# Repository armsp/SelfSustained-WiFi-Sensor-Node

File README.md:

# Self Sustained WiFi Sensor Node using CC3200 SoC and Energy Harvesting with BQ25505/BQ25570
Complete Details regarding the project can be found at my Blog https://shantamraj.wordpress.com
You can also visit my Hackster.io profile for the same at https://www.hackster.io/shantam

I am working on taking this project and the overall idea behind it to next level. The updates regarding that will be posted soon.

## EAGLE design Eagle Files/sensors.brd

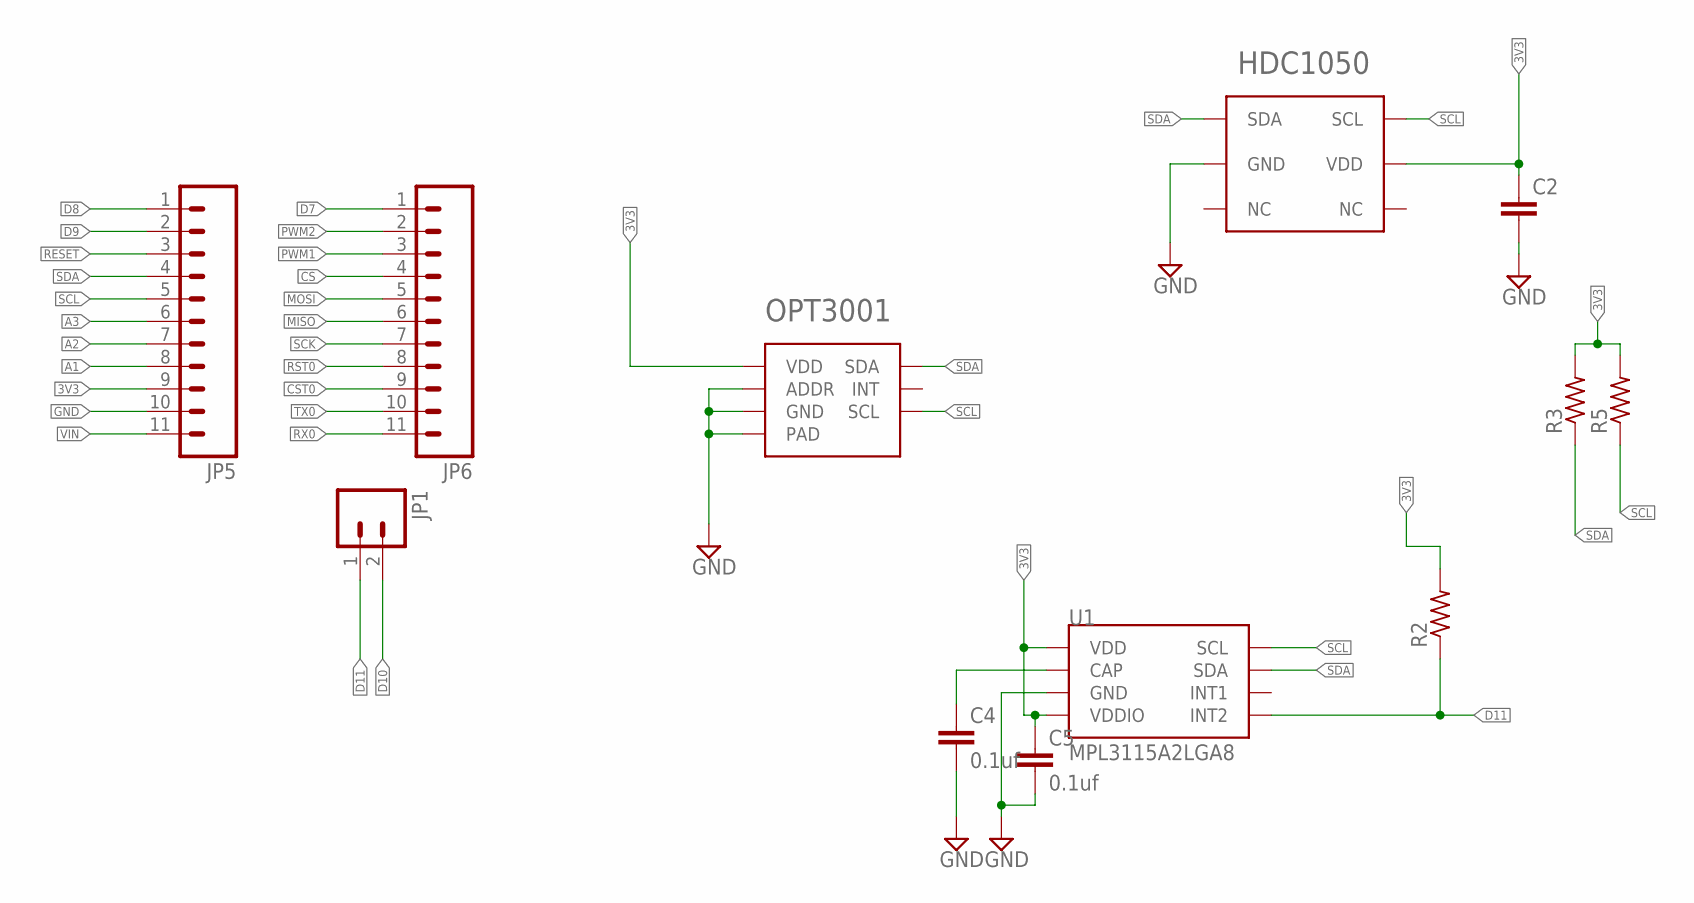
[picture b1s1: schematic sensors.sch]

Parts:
C2: C-EUC0805; C0805
C4, C5: 0.1uf; C0805
HDC1050: HDC1050; PWSON-6
JP1: M02PTH; 1X02
JP5, JP6: M11PTH; 1X11
OPT3001: OPT3001
R2, R3, R5: R-US_0204/5; 0204/5
U1: MPL3115A2LGA8; LGA8

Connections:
3V3: C2.1, C5.1, HDC1050.P$5 (VDD), JP5.9, OPT3001.P$1 (VDD), R2.2, R3.2, R5.2, U1.1 (VDD), U1.4 (VDDIO)
A1: JP5.8
A2: JP5.7
A3: JP5.6
CS: JP6.4
CST0: JP6.9
D7: JP6.1
D8: JP5.1
D9: JP5.2
D10: JP1.2
D11: JP1.1, R2.1, U1.5 (INT2)
GND: C2.2, C4.2, C5.2, HDC1050.P$2 (GND), JP5.10, OPT3001.P$2 (ADDR), OPT3001.P$3 (GND), OPT3001.P$7 (PAD), U1.3 (GND)
MISO: JP6.6
MOSI: JP6.5
unnamed: C4.1, U1.2 (CAP)
PWM1: JP6.3
PWM2: JP6.2
RESET: JP5.3
RST0: JP6.8
RX0: JP6.11
SCK: JP6.7
SCL: HDC1050.P$6 (SCL), JP5.5, OPT3001.P$4 (SCL), R5.1, U1.8 (SCL)
SDA: HDC1050.P$1 (SDA), JP5.4, OPT3001.P$6 (SDA), R3.1, U1.7 (SDA)
TX0: JP6.10
VIN: JP5.11

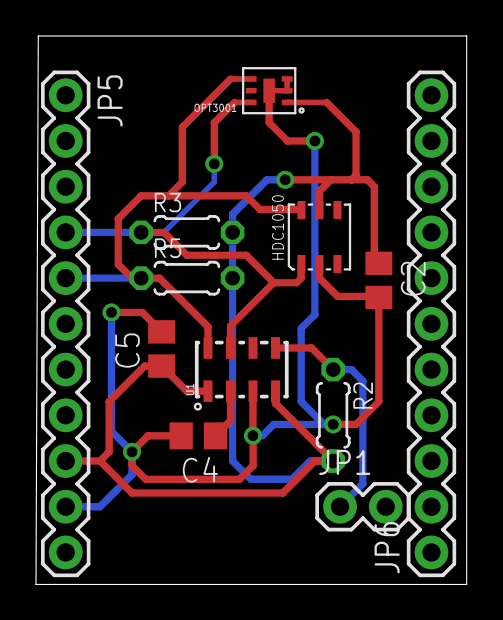
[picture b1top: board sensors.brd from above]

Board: 2 copper layers, 23.9 x 30.5 mm, 12 parts (0 on the bottom side), 6 nets.

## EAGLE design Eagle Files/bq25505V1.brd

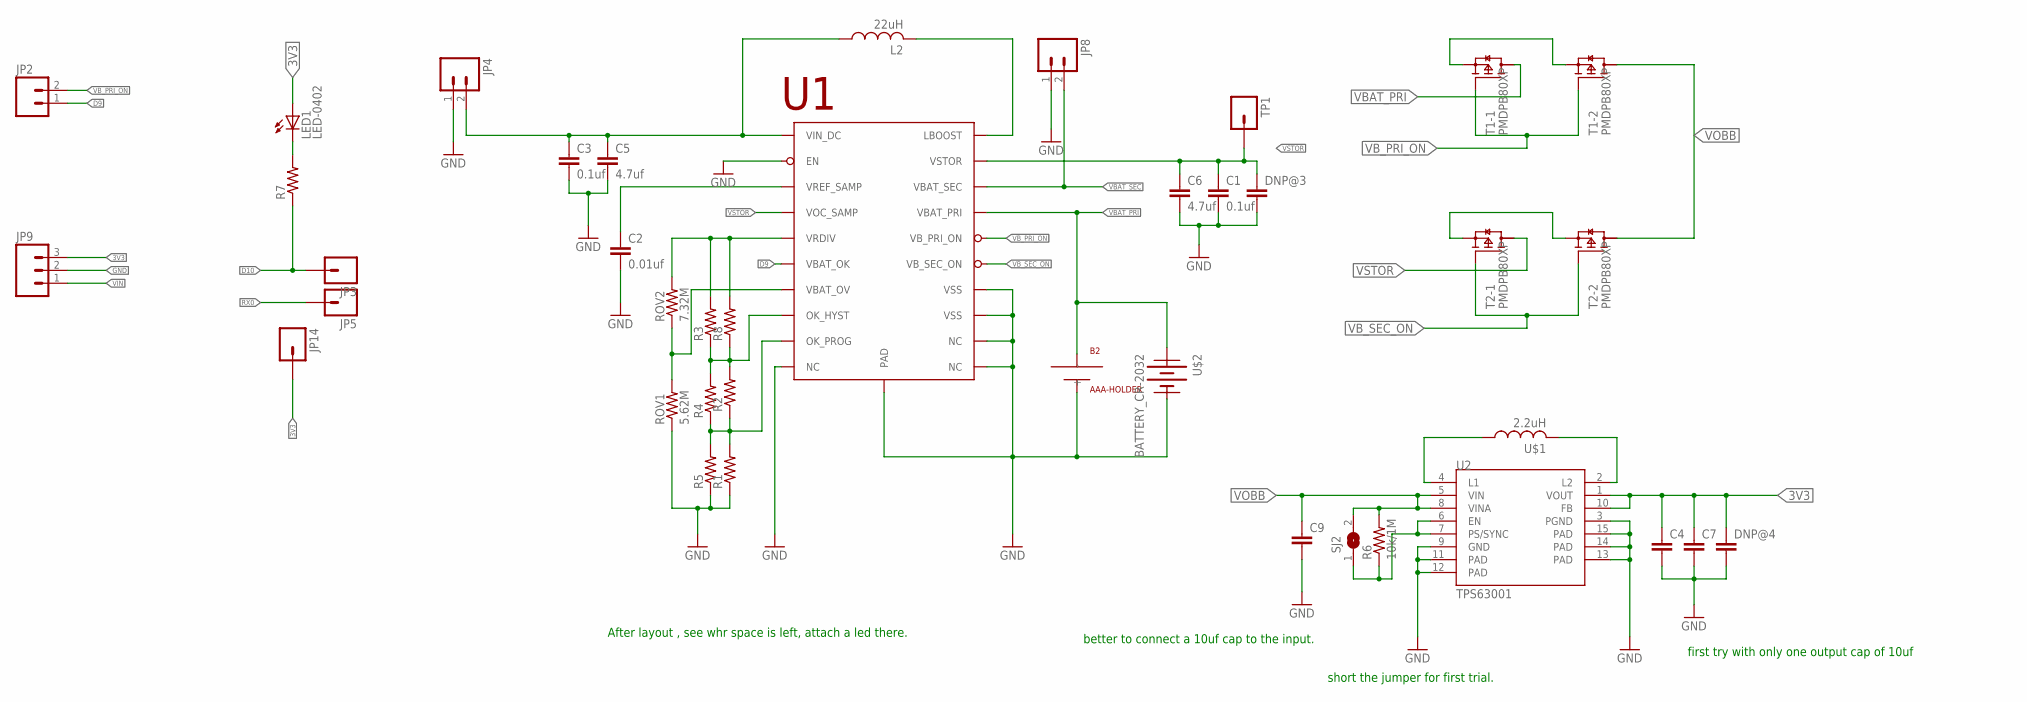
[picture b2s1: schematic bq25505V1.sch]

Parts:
B2: AAA-HOLDER; AAA-BATTERY
C1, C3: 0.1uf; C0805
C2: 0.01uf; C0805
C4, C7, C9: C-EUC0805; C0805
C5, C6: 4.7uf; C0805
DNP@3, DNP@4: C-EUC0805; C0805
JP2: M02PTH; 1X02
JP3, JP5, JP14: M01PTH; 1X01
JP4, JP8: M02-JST-2-PTH-NO_SILK; JST-2-PTH-NS
JP9: M03PTH; 1X03
L2: 22uH; LPS6235
LED1: LED-0402; 0402
R1, R3, R5, R7: R-US_R0603; R0603
R2, R8: R-US_R0805; R0805
R4: R-US_R1206; R1206
R6: 10k/1M; R0805
ROV1: 5.62M; R1206
ROV2: 7.32M; R1206
SJ2: SJ
T1, T2: PMDPB80XP; SOT1118
TP1: M01PTH; 1X01
U1: BQ25505; VQFN-20
U2: TPS63001; QFN-10_PAD
U$1: 2.2uH; LPS3010
U$2: BATTERY_CR-2032; BATTCON_20MM

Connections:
3V3: C4.1, C7.1, DNP@4.1, JP9.3, JP14.1, LED1.P$1 (A), U2.1 (VOUT), U2.10 (FB)
D9: JP2.1, U1.P$13 (VBAT_OK)
D10: JP3.1, R7.1
GND: B2.P$2 (-), C1.2, C2.2, C3.2, C4.2, C5.2, C6.2, C7.2, C9.2, DNP@3.2, DNP@4.2, JP4.1, JP8.1, JP9.2, R1.1, R5.1, ROV1.1, U1.P$1 (VSS), U1.P$5 (EN), U1.P$6 (NC), U1.P$15 (VSS), U1.P$16 (NC), U1.P$17 (NC), U1.P$21 (PAD), U2.3 (PGND), U2.9 (GND), U2.11 (PAD), U2.12 (PAD), U2.13 (PAD), U2.14 (PAD), U2.15 (PAD), U$2.2 (-2)
L1: U2.4 (L1), U$1.P$1 (1)
L2: U2.2 (L2), U$1.P$2 (2)
LBOOST: L2.P$2 (2), U1.P$20 (LBOOST)
unnamed: C2.1, U1.P$4 (VREF_SAMP)
unnamed: T1.1 (S), T1.4 (S)
unnamed: T2.1 (S), T2.4 (S)
unnamed: LED1.P$2 (C), R7.2
OK_HYST: R2.2, R3.1, R4.2, R8.1, U1.P$11 (OK_HYST)
OK_PROG: R1.2, R2.1, R4.1, R5.2, U1.P$12 (OK_PROG)
PS/SYNC: R6.1, SJ2.1, U2.6 (EN), U2.7 (PS/SYNC)
RX0: JP5.1
VBAT_OV: ROV1.2, ROV2.1, U1.P$7 (VBAT_OV)
VBAT_PRI: B2.P$1 (+), T1.6 (D), T1.7 (D), U1.P$14 (VBAT_PRI), U$2.1 (+2), U$2.3 (+2)
VBAT_SEC: JP8.2, U1.P$18 (VBAT_SEC)
VB_PRI_ON: JP2.2, T1.2 (G), T1.5 (G), U1.P$10 (VB_PRI_ON)
VB_SEC_ON: T2.2 (G), T2.5 (G), U1.P$9 (VB_SEC_ON)
VIN: JP9.1
VIN_DC: C3.1, C5.1, JP4.2, L2.P$1 (1), U1.P$2 (VIN_DC)
VOBB: C9.1, R6.2, SJ2.2, T1.3 (D), T1.8 (D), T2.3 (D), T2.8 (D), U2.5 (VIN), U2.8 (VINA)
VRDIV: R3.2, R8.2, ROV2.2, U1.P$8 (VRDIV)
VSTOR: C1.1, C6.1, DNP@3.1, T2.6 (D), T2.7 (D), TP1.1, U1.P$3 (VOC_SAMP), U1.P$19 (VSTOR)

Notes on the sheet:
After layout , see whr space is left, attach a led there.
first try with only one output cap of 10uf
short the jumper for first trial.
better to connect a 10uf cap to the input.

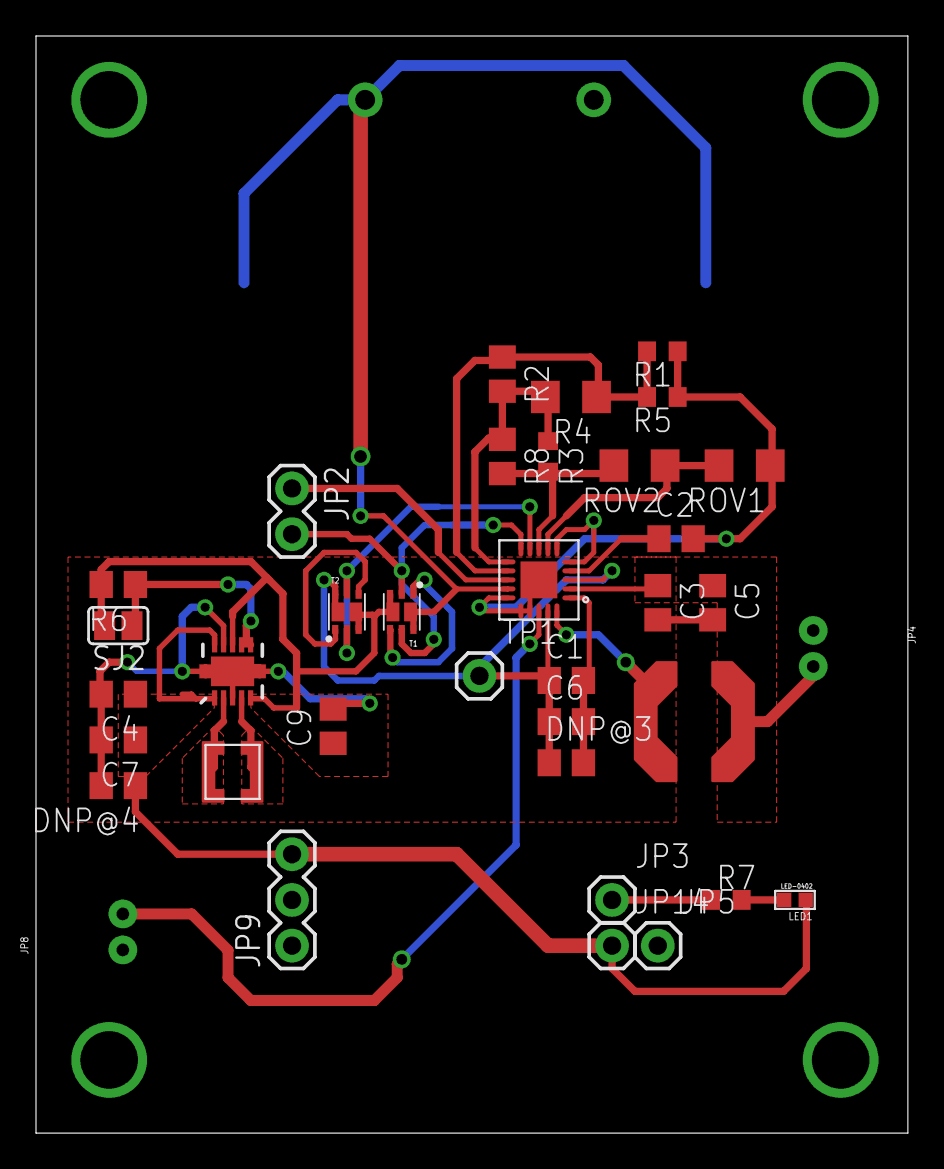
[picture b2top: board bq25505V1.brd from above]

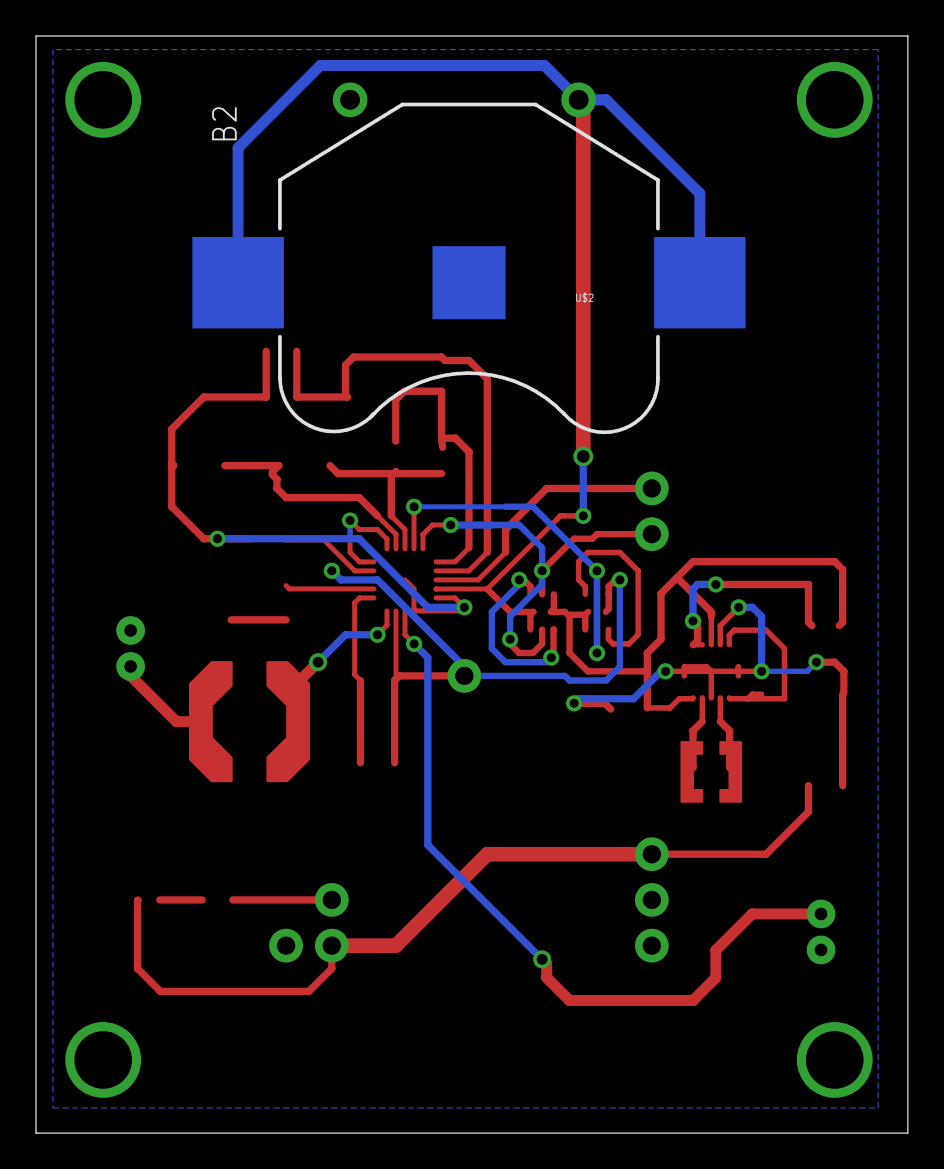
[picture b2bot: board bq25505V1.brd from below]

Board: 2 copper layers, 48.4 x 61.0 mm, 38 parts (2 on the bottom side), 23 nets.

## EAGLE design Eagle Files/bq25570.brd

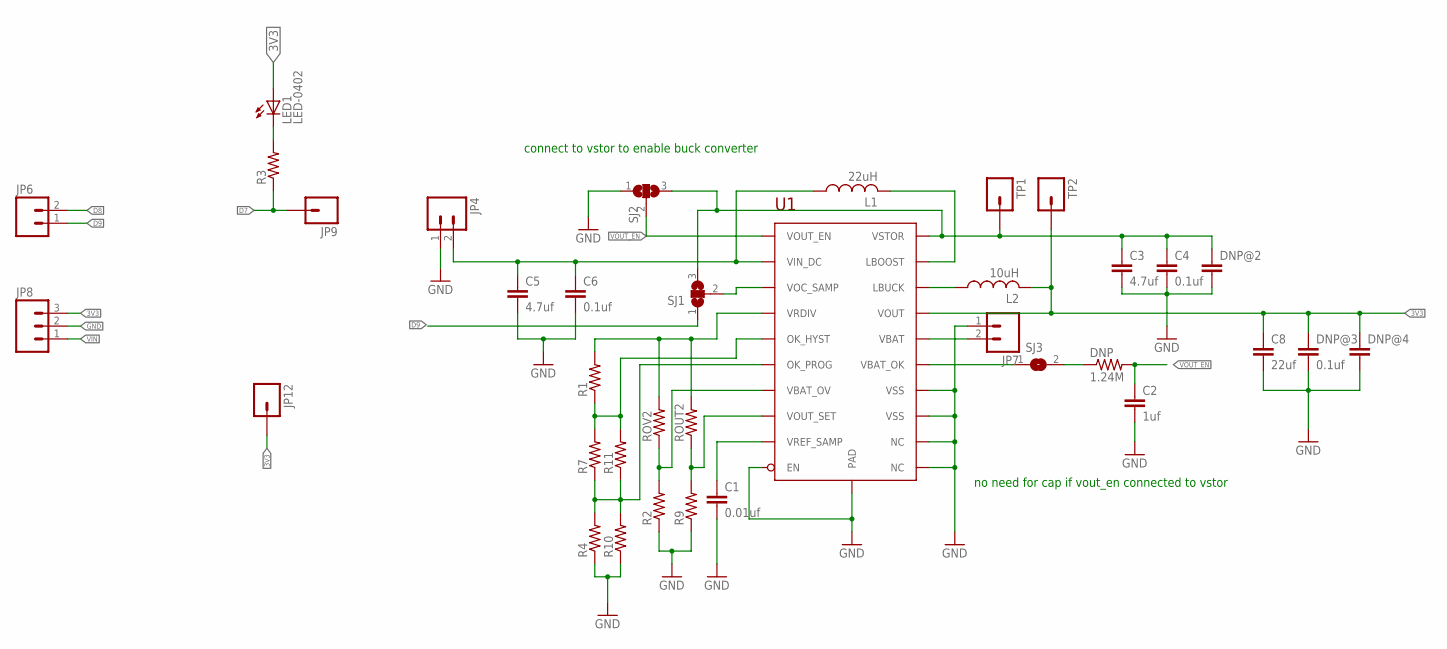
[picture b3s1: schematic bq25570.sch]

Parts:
C1: 0.01uf; C0805
C2: 1uf; C0805
C3, C5: 4.7uf; C0805
C4, C6: 0.1uf; C0805
C8: 22uf; C0805
DNP: 1.24M; M0805
DNP@2, DNP@4: C-EUC0805; C0805
DNP@3: 0.1uf; C0805
JP4, JP7: M02-JST-2-PTH-NO_SILK; JST-2-PTH-NS
JP6: M02PTH; 1X02
JP8: M03PTH; 1X03
JP9, JP12: M01PTH; 1X01
L1: 22uH; LPS6235
L2: 10uH; LPS6235
LED1: LED-0402; 0402
R1, R2, R3, R4: R-US_R0603; R0603
R7, R9, R10: R-US_R0805; R0805
R11: R-US_R1206; R1206
ROUT2: R-US_R0603; R0603
ROV2: R-US_R0805; R0805
SJ1, SJ2: SJ2W; SJ_2
SJ3: SJ
TP1, TP2: M01PTH; 1X01
U1: BQ25570; QFN-20

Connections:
3V3: C8.1, DNP@3.1, DNP@4.1, JP8.3, JP12.1, L2.P$2 (2), LED1.P$1 (A), TP2.1, U1.P$14 (VOUT)
D7: JP9.1, R3.1
D8: JP6.2
D9: JP6.1, SJ1.1
GND: C1.2, C2.2, C3.2, C4.2, C5.2, C6.2, C8.2, DNP@2.2, DNP@3.2, DNP@4.2, JP4.1, JP7.1, JP8.2, R2.1, R4.1, R9.1, R10.1, SJ2.1, U1.P$1 (VSS), U1.P$5 (EN), U1.P$9 (NC), U1.P$15 (VSS), U1.P$17 (NC), U1.P$21 (PAD)
unnamed: L1.P$2 (2), U1.P$20 (LBOOST)
unnamed: L2.P$1 (1), U1.P$16 (LBUCK)
unnamed: SJ1.2, U1.P$3 (VOC_SAMP)
unnamed: JP7.2, U1.P$18 (VBAT)
unnamed: C1.1, U1.P$4 (VREF_SAMP)
unnamed: SJ3.1, U1.P$13 (VBAT_OK)
unnamed: R1.2, ROUT2.2, ROV2.2, U1.P$8 (VRDIV)
unnamed: DNP.1, SJ3.2
unnamed: R9.2, ROUT2.1, U1.P$12 (VOUT_SET)
unnamed: R2.2, ROV2.1, U1.P$7 (VBAT_OV)
unnamed: R1.1, R7.2, R11.2, U1.P$10 (OK_HYST)
unnamed: LED1.P$2 (C), R3.2
unnamed: R4.2, R7.1, R10.2, R11.1, U1.P$11 (OK_PROG)
VIN: JP8.1
VIN_DC: C5.1, C6.1, JP4.2, L1.P$1 (1), U1.P$2 (VIN_DC)
VOUT_EN: C2.1, DNP.2, SJ2.2, U1.P$6 (VOUT_EN)
VSTOR: C3.1, C4.1, DNP@2.1, SJ1.3, SJ2.3, TP1.1, U1.P$19 (VSTOR)

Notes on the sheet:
connect to vstor to enable buck converter
no need for cap if vout_en connected to vstor

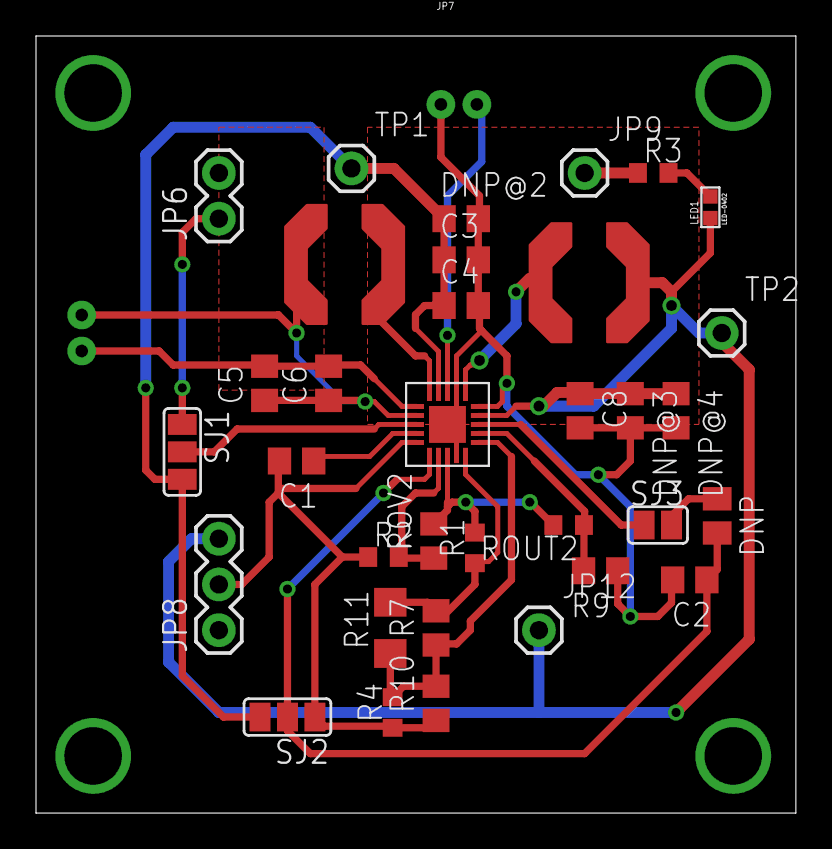
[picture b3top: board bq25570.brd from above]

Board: 2 copper layers, 42.2 x 43.2 mm, 36 parts (0 on the bottom side), 20 nets.

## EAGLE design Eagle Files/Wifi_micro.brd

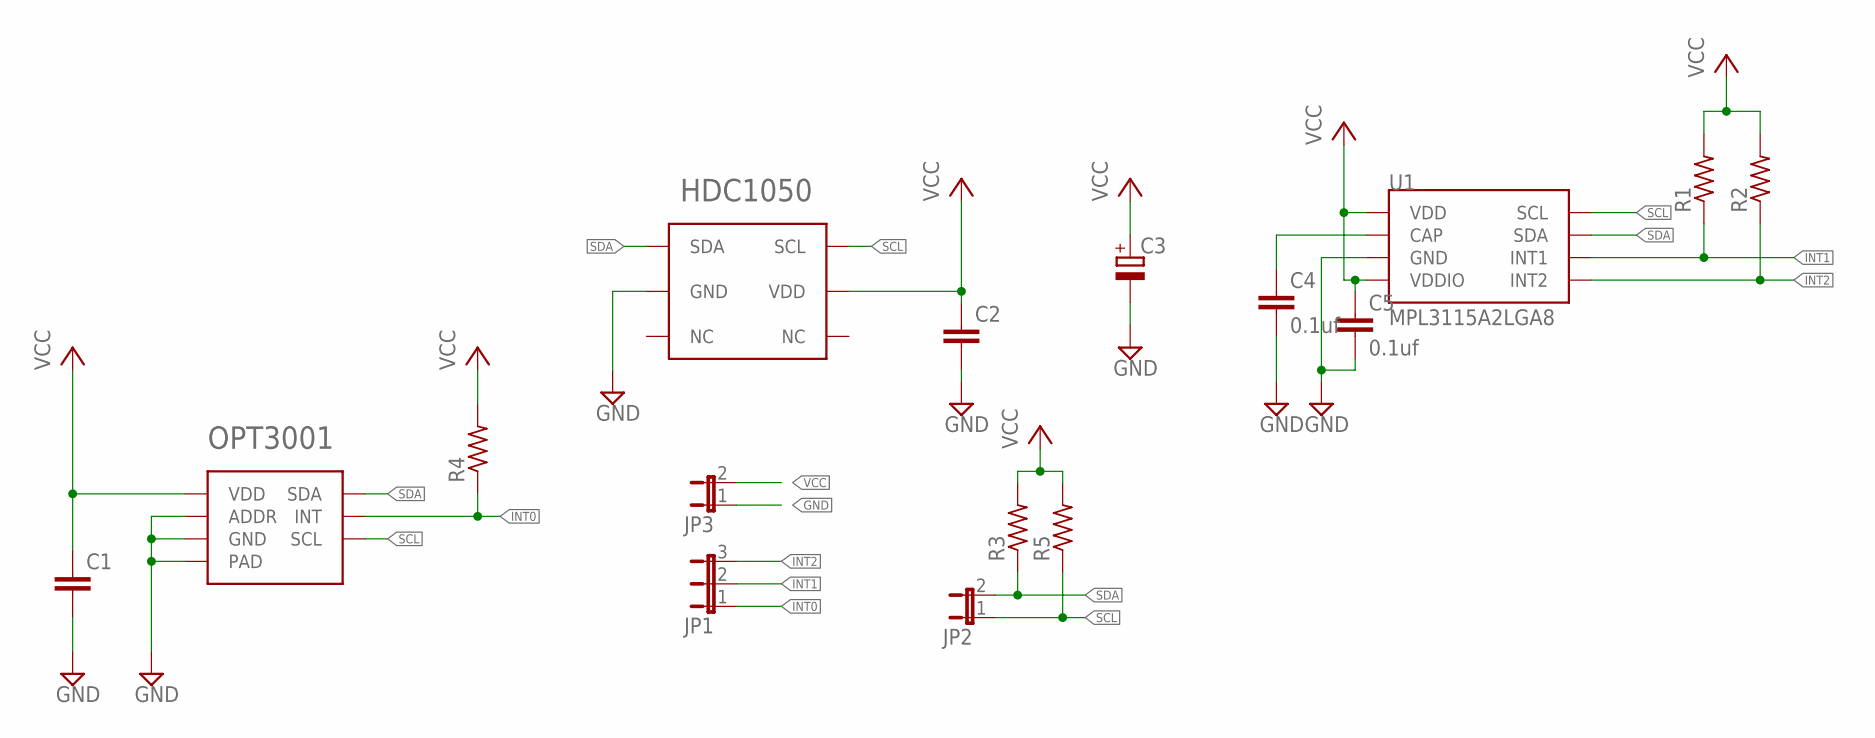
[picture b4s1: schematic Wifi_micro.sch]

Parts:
C1, C2: C-EUC1206; C1206
C3: CPOL-EUE2.5-5; E2,5-5
C4, C5: 0.1uf; C1206
HDC1050: HDC1050; PWSON-6
JP1: JP2E; JP2
JP2, JP3: JP1E; JP1
OPT3001: OPT3001
R1, R2, R3, R4, R5: R-US_0204/5; 0204/5
U1: MPL3115A2LGA8; LGA8

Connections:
GND: C1.2, C2.2, C3.-, C4.2, C5.2, HDC1050.P$2 (GND), JP3.1, OPT3001.P$2 (ADDR), OPT3001.P$3 (GND), OPT3001.P$7 (PAD), U1.3 (GND)
INT0: JP1.1, OPT3001.P$5 (INT), R4.1
INT1: JP1.2, R1.1, U1.6 (INT1)
INT2: JP1.3, R2.1, U1.5 (INT2)
unnamed: C4.1, U1.2 (CAP)
SCL: HDC1050.P$6 (SCL), JP2.1, OPT3001.P$4 (SCL), R5.1, U1.8 (SCL)
SDA: HDC1050.P$1 (SDA), JP2.2, OPT3001.P$6 (SDA), R3.1, U1.7 (SDA)
VCC: C1.1, C2.1, C3.+, C5.1, HDC1050.P$5 (VDD), JP3.2, OPT3001.P$1 (VDD), R1.2, R2.2, R3.2, R4.2, R5.2, U1.1 (VDD), U1.4 (VDDIO)

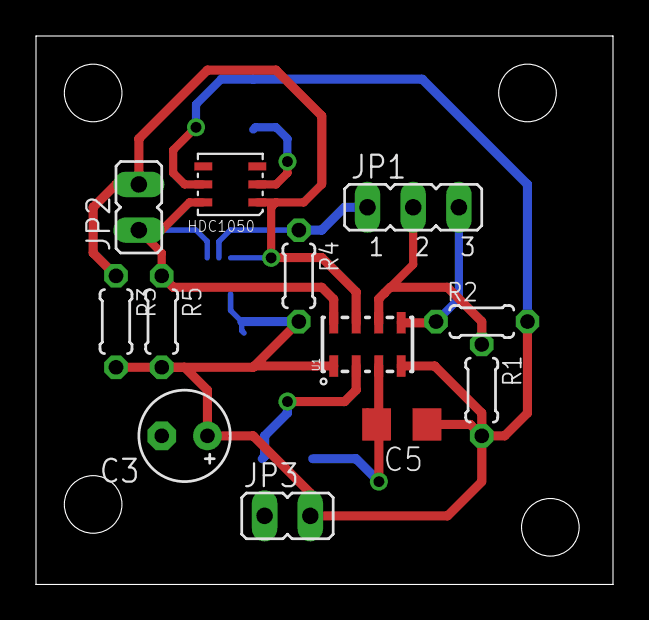
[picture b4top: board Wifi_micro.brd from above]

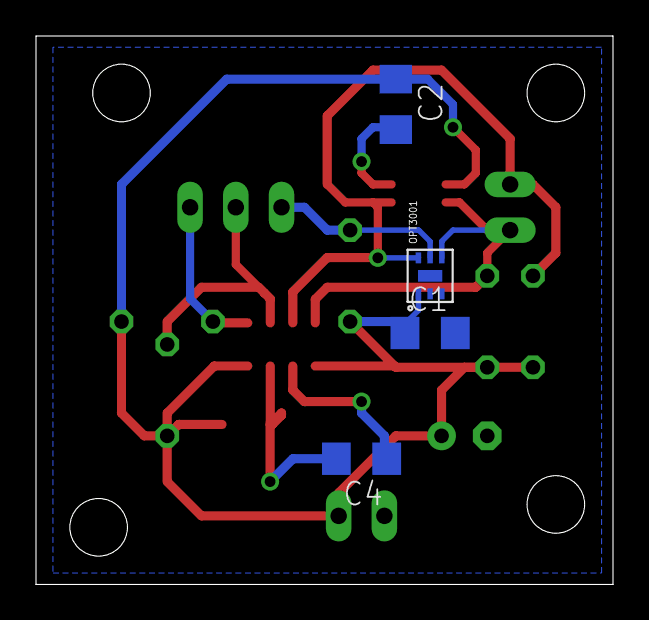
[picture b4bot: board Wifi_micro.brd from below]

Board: 2 copper layers, 32.1 x 30.5 mm, 16 parts (4 on the bottom side), 8 nets.

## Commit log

2016-09-07 Added Eagle files and pics.
2016-09-07 Added Energia code and HTML file for real time graping

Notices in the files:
parts and their libraries:
SparkFun-Sensors: Licensing: Creative Commons ShareAlike 4.0 International - https://creativecommons.org/licenses/by-sa/4.0
NXP_60_26022015: This library may be distributed and adapted freely for any purpose, as long as NXP is credited and any new creation is licensed under the same terms.
